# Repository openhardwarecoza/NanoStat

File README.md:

# NanoStat
Arduino Nano Thermostat

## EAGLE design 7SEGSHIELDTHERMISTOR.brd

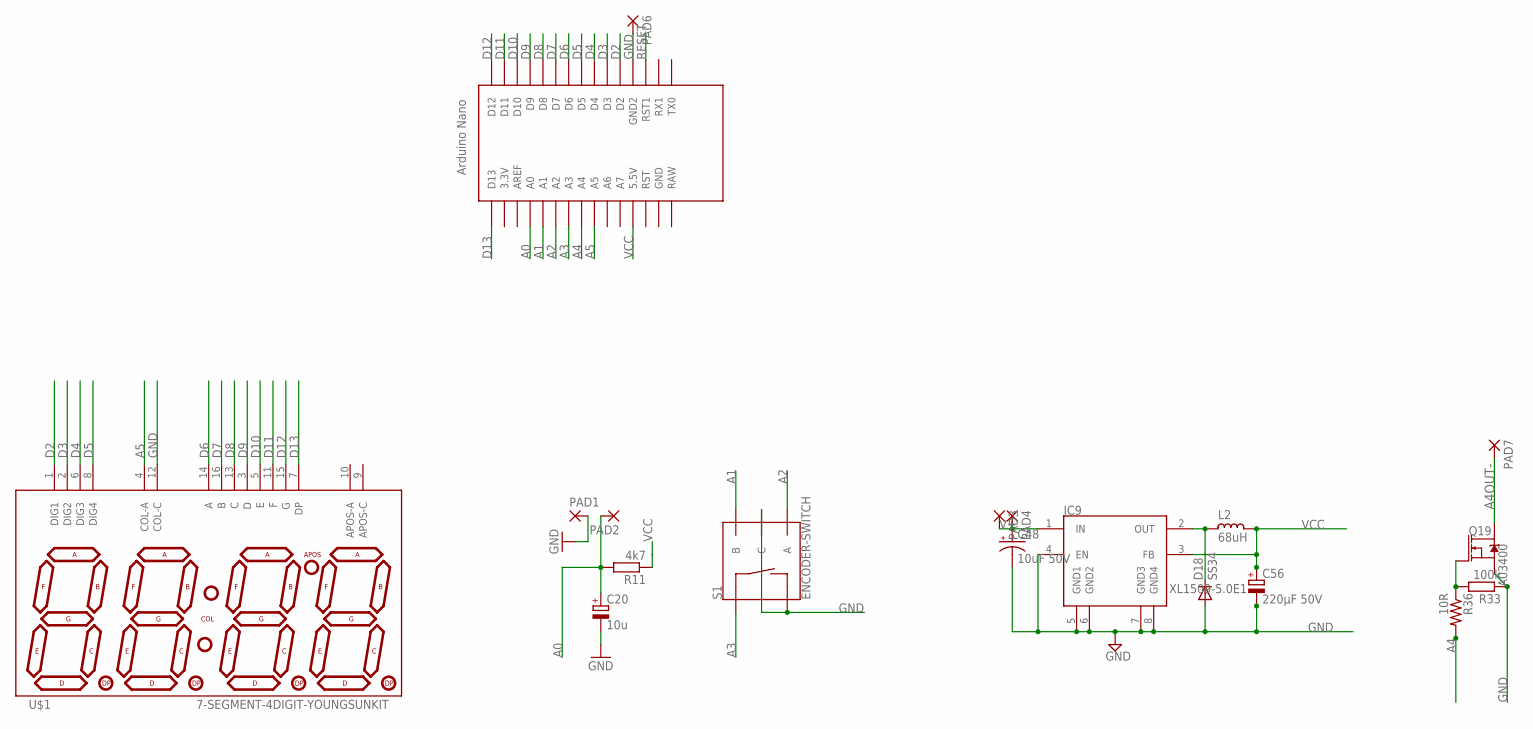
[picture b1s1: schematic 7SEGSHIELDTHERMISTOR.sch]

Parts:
C20: 10u; A/3216-18W
C48: 10uF 50V; EIA3216
C56: 220µF 50V; E2,5-6E
D18: SS34; DO-214AC
IC9: XL1509-5.0E1; SO08
L2: 68uH; CD75
PAD1, PAD2, PAD3, PAD4, PAD6, PAD7: 2,54/1,1
Q19: A03400; SOT23-3@1
R11: 4k7; M1206
R33: 100k; R1206
R36: 10R; R1206@1
S1: ENCODER-SWITCH; ROTARY_ENC_PLAIN
U$1: 7-SEGMENT-4DIGIT-YOUNGSUNKIT; 7-SEGMENT-4DIGIT-YOUNGSUN-KIT
U$2: NANO

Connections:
A0: C20.+, PAD2.1, R11.2, U$2.A0
A1: S1.B, U$2.A1
A2: S1.A, U$2.A2
A3: S1.SW+, U$2.A3
A4: R36.2, U$2.A4
A4OUT-: PAD7.1, Q19.3 (D)
A5: U$1.4 (COL-A), U$2.A5
D2: U$1.1 (DIG1), U$2.D2
D3: U$1.2 (DIG2), U$2.D3
D4: U$1.6 (DIG3), U$2.D4
D5: U$1.8 (DIG4), U$2.D5
D6: U$1.14 (A), U$2.D6
D7: U$1.16 (B), U$2.D7
D8: U$1.13 (C), U$2.D8
D9: U$1.3 (D), U$2.D9
D10: U$1.5 (E), U$2.D10
D11: U$1.11 (F), U$2.D11
D12: U$1.15 (G), U$2.D12
D13: U$1.7 (DP), U$2.D13
GND: C20.-, C48.C (-), C56.-, D18.2 (A), IC9.4 (EN), IC9.5 (GND1), IC9.6 (GND2), IC9.7 (GND3), IC9.8 (GND4), PAD1.1, PAD6.1, Q19.2 (S), R33.1, S1.C, S1.SW-, U$1.12 (COL-C), U$2.GND1 (GND2)
unnamed: D18.1 (C), IC9.2 (OUT), L2.2
unnamed: Q19.1 (G), R33.2, R36.1
RESET: U$2.RST1
V+: C48.A (+), IC9.1 (IN), PAD3.1, PAD4.1
VCC: C56.+, IC9.3 (FB), L2.1, R11.1, U$2.5V (5.5V)

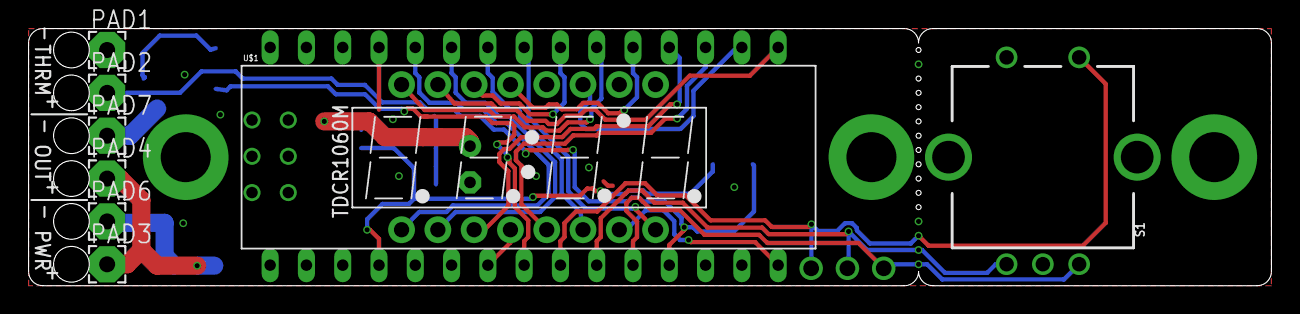
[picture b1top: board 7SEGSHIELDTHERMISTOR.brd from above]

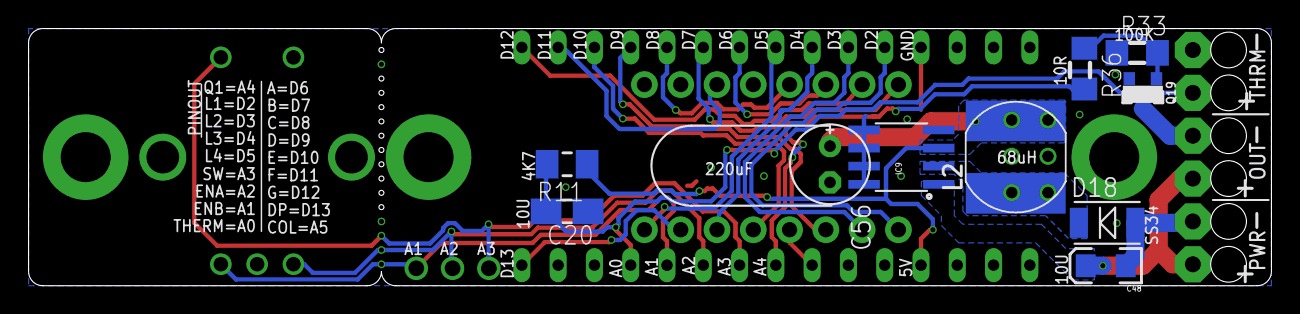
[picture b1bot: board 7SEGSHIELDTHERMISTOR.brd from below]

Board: 2 copper layers, 87.0 x 18.0 mm, 19 parts (11 on the bottom side), 24 nets.

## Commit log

2018-10-23 archive

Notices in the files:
parts and their libraries:
SparkFun-Switches: Licensing: Creative Commons ShareAlike 4.0 International - https://creativecommons.org/licenses/by-sa/4.0
rc-master-smd: Copyright (C) 2007, Bob Starr
SparkFun-Aesthetics: Licensing: CC v3.0 Share-Alike You are welcome to use this library for commercial purposes.
